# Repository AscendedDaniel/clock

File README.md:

clock
=====

An open source hardware countdown clock.

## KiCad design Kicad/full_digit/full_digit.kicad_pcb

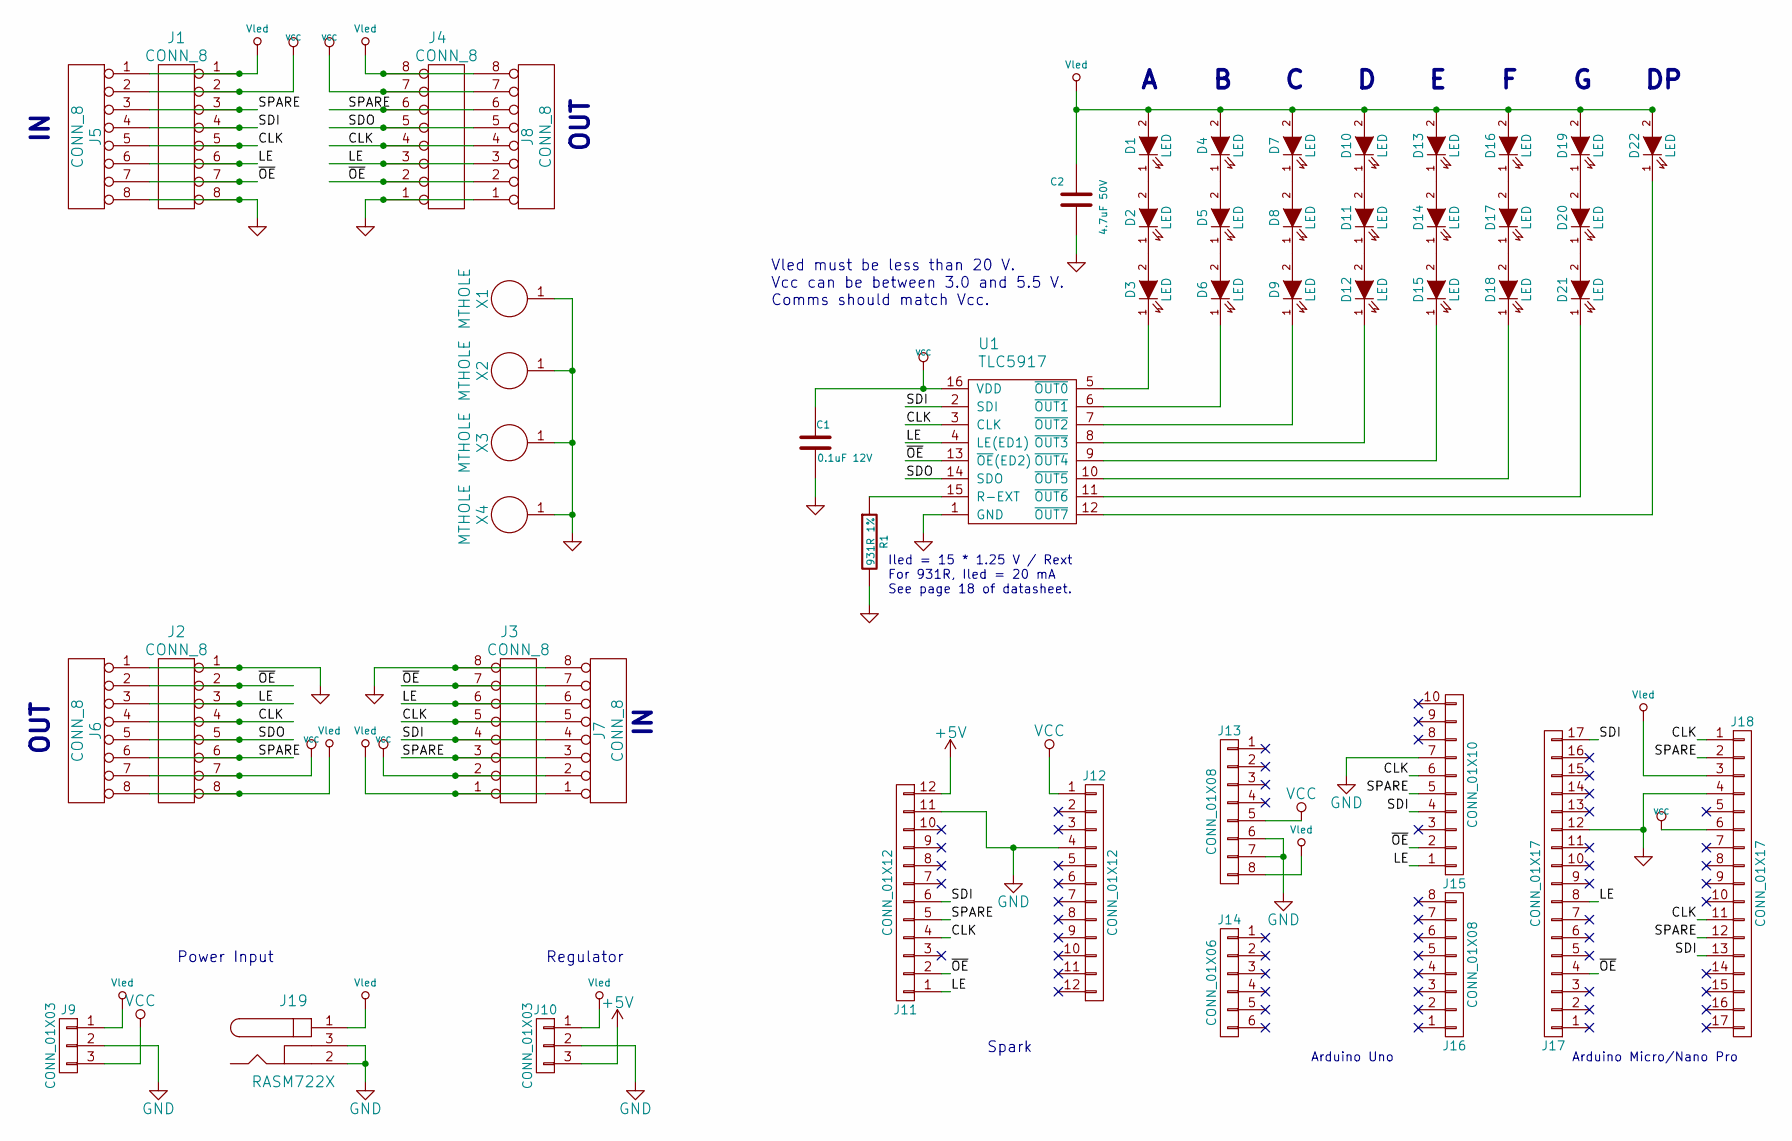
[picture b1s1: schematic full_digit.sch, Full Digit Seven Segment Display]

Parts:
C1: 0.1uF 12V; C_0603
C2: 4.7uF 50V; C_1206_HandSoldering
D1, D2, D3, D4, D5, D6, D7, D8, D9, D10, D11, D12, D13, D14, D15, D16, D17, D18, D19, D20, D21, D22: LED; 1206_LED_Reverse
J1, J2, J3, J4: CONN_8; SSM-SH-08
J5, J6, J7, J8: CONN_8; HEADER_8X1
J9, J10: CONN_01X03; HEADER_SMT_01x03
J11, J12: CONN_01X12; HEADER_SMT_01x12_SV
J13, J16: CONN_01X08; HEADER_SMT_01x08
J14: CONN_01X06; HEADER_SMT_01x06
J15: CONN_01X10; HEADER_SMT_01x10
J17, J18: CONN_01X17; HEADER_SMT_01x17
J19: RASM722X; RASM722
R1: 931R 1%; C_0603
U1: TLC5917; SOIC16_Jason
X1, X2, X3, X4: MTHOLE; MTHOLE_3mm

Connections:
+5V: J10.3, J11.12
/CLK: J1.5, J2.4, J3.5, J4.4, J5.5, J6.4, J7.5, J8.4, J11.4, J15.6, J18.1, J18.11, U1.3 (CLK)
/LE: J1.6, J2.3, J3.6, J4.3, J5.6, J6.3, J7.6, J8.3, J11.1, J15.1, J17.8, U1.4 (LE(ED1))
/SDI: J1.4, J3.4, J5.4, J7.4, J11.6, J15.4, J17.17, J18.13, U1.2 (SDI)
/SDO: J2.5, J4.5, J6.5, J8.5, U1.14 (SDO)
/SPARE: J1.3, J2.6, J3.3, J4.6, J5.3, J6.6, J7.3, J8.6, J11.5, J15.5, J18.2, J18.12
/~OE: J1.7, J2.2, J3.7, J4.2, J5.7, J6.2, J7.7, J8.2, J11.2, J15.2, J17.4, U1.13 (~OE~(ED2))
GND: C1.2, C2.2, J1.8, J2.1, J3.8, J4.1, J5.8, J6.1, J7.8, J8.1, J9.2, J10.2, J11.11, J12.4, J13.6, J13.7, J15.7, J17.12, J18.4, J19.2, J19.3, R1.2, U1.1 (GND), X1.1, X2.1, X3.1, X4.1
unnamed: D1.1 (K), D2.2 (A)
unnamed: D2.1 (K), D3.2 (A)
unnamed: D3.1 (K), U1.5 (~OUT0)
unnamed: D4.1 (K), D5.2 (A)
unnamed: D5.1 (K), D6.2 (A)
unnamed: D6.1 (K), U1.6 (~OUT1)
unnamed: D7.1 (K), D8.2 (A)
unnamed: D8.1 (K), D9.2 (A)
unnamed: D9.1 (K), U1.7 (~OUT2)
unnamed: D10.1 (K), D11.2 (A)
unnamed: D11.1 (K), D12.2 (A)
unnamed: D12.1 (K), U1.8 (~OUT3)
unnamed: D13.1 (K), D14.2 (A)
unnamed: D14.1 (K), D15.2 (A)
unnamed: D15.1 (K), U1.9 (~OUT4)
unnamed: D16.1 (K), D17.2 (A)
unnamed: D17.1 (K), D18.2 (A)
unnamed: D18.1 (K), U1.10 (~OUT5)
unnamed: D19.1 (K), D20.2 (A)
unnamed: D20.1 (K), D21.2 (A)
unnamed: D21.1 (K), U1.11 (~OUT6)
unnamed: D22.1 (K), U1.12 (~OUT7)
unnamed: R1.1, U1.15 (R-EXT)
VCC: C1.1, J1.2, J2.7, J3.2, J4.7, J5.2, J6.7, J7.2, J8.7, J9.3, J12.1, J13.5, J18.6, U1.16 (VDD)
Vled: C2.1, D1.2 (A), D4.2 (A), D7.2 (A), D10.2 (A), D13.2 (A), D16.2 (A), D19.2 (A), D22.2 (A), J1.1, J2.8, J3.1, J4.8, J5.1, J6.8, J7.1, J8.8, J9.1, J10.1, J13.8, J18.3, J19.1

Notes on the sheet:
OUT
Iled = 15 * 1.25 V / Rext For 931R, Iled = 20 mA See page 18 of datasheet.
Vled must be less than 20 V. Vcc can be between 3.0 and 5.5 V. Comms should match Vcc.
Spark
Regulator
Arduino Uno
Arduino Micro/Nano Pro
Power Input

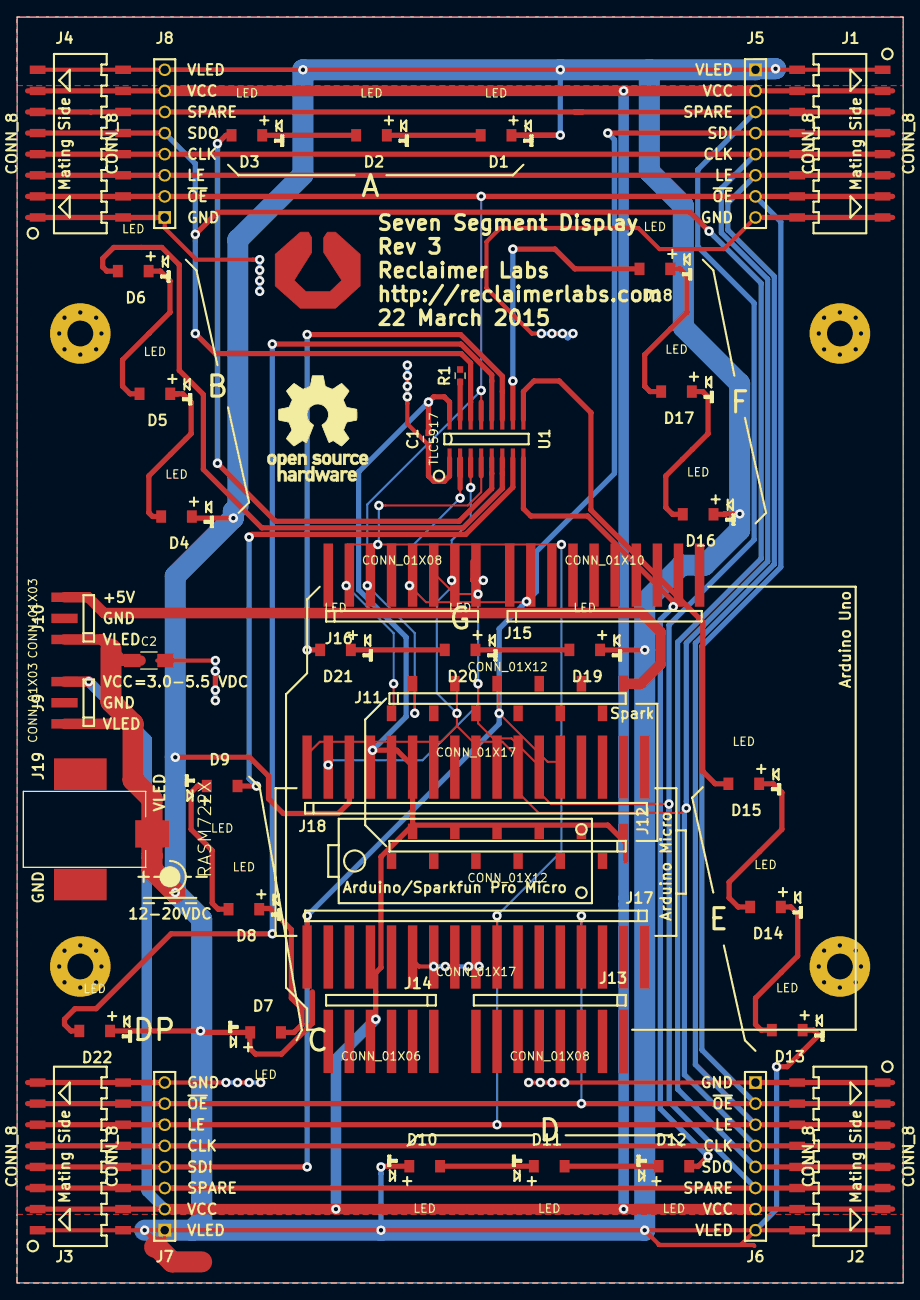
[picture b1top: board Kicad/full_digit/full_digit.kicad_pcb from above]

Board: 2 copper layers, 106.7 x 152.4 mm, 49 parts (0 on the bottom side), 33 nets.

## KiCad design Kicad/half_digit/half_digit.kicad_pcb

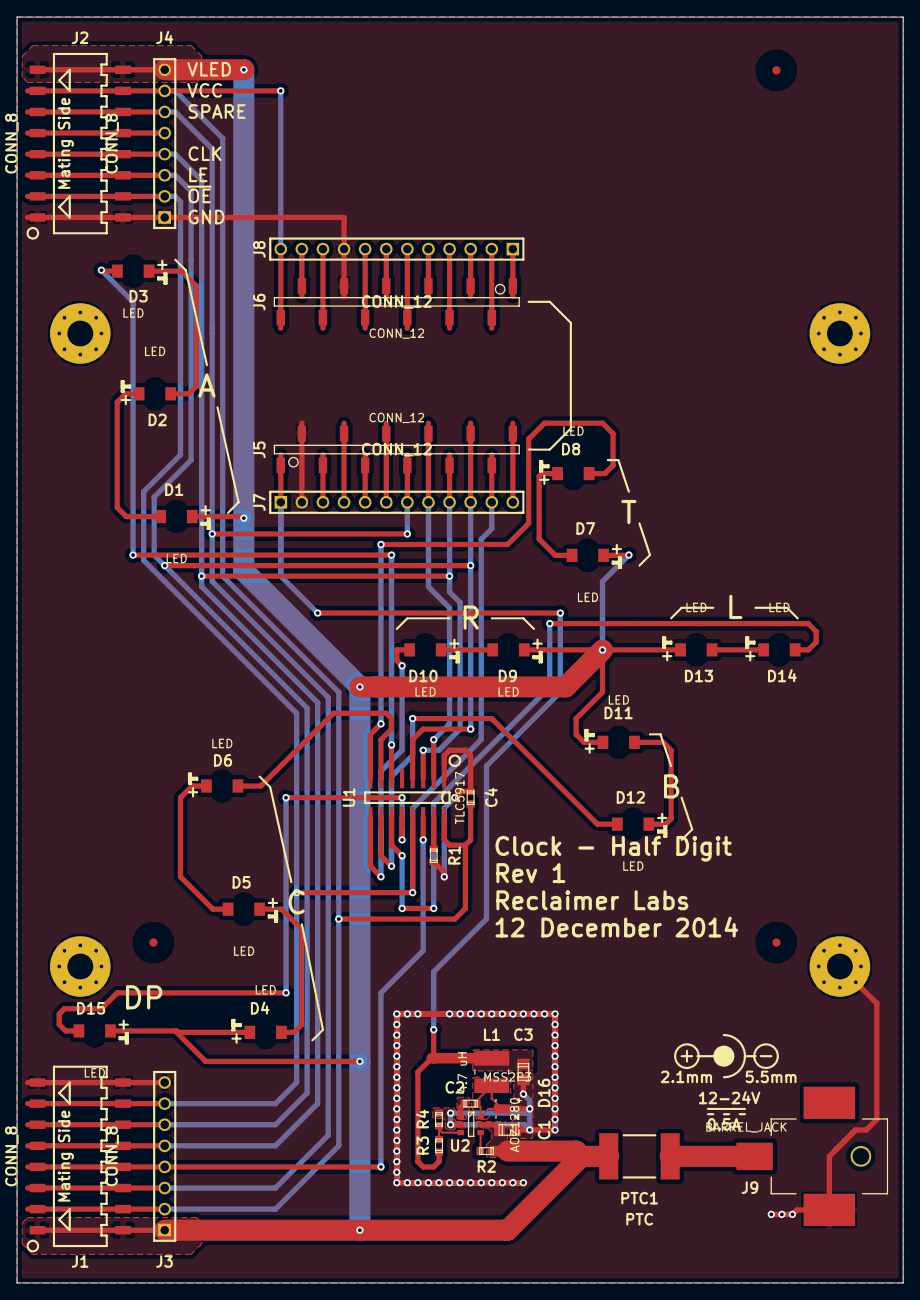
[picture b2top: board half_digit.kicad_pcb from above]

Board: 2 copper layers, 106.7 x 152.4 mm, 44 parts (0 on the bottom side), 47 nets.

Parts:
C1, C3: 4.7uF; c_0805
C2: 10nF; c_0603
C4: 0.1uF; c_0603
D1, D2, D3, D4, D5, D6, D7, D8, D9, D10, D11, D12, D13, D14, D15: LED; 1206_LED_Reverse
D16: MSS2P3
FIDUCIAL: VAL**; FIDUCIAL
FIDUCIAL#2, FIDUCIAL#3: VAL**; FIDUCIAL
J1, J2: CONN_8; SSM-SH-08
J3, J4: CONN_8; HEADER_8X1
J5, J6: CONN_12; SSM-SV-12
J7, J8: CONN_12; HEADER_12X1
J9: BARREL_JACK; PJ-036AH-SMT
L1: 4.7 uH; 1515
PTC1: PTC; 2920_ptc
R1: 931R 1%; c_0603
R2, R4: 9.53k 1%; c_0603
R3: 49.9k 1%; c_0603
U1: TLC5917; SOIC16_Jason
U2: AOZ1280; SOT23_6_Jason
X1, X2, X3, X4: MTHOLE; MTHOLE_3mm

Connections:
+5V: C3.1, J5.1, J7.1, L1.2, R3.1
/CLK: J1.5, J2.4, J3.5, J4.4, J5.9, J7.9, U1.3
/LE: J1.6, J2.3, J3.6, J4.3, J5.10, J7.10, U1.4
/SDI: J5.8, J7.8, U1.2
/SDO: J1.4, J3.4, U1.14
/SPARE: J1.3, J2.6, J3.3, J4.6, J5.7, J7.7
/~OE: J1.7, J2.2, J3.7, J4.2, J5.11, J7.11, U1.13
GND: C1.2, C3.2, C4.2, D16.1, J1.8, J2.1, J3.8, J4.1, J5.2, J6.9, J7.2, J8.9, J9.2, R1.2, R4.2, U1.1, U2.2, X1.1, X2.1, X3.1, X4.1
unnamed: D15.2, U1.12
unnamed: D14.2, U1.11
unnamed: D12.2, U1.10
unnamed: D10.2, U1.9
unnamed: D8.2, U1.8
unnamed: D6.2, U1.7
unnamed: D3.2, U1.6
unnamed: R1.1, U1.15
unnamed: J5.5, J7.5
unnamed: J5.4, J7.4
unnamed: J5.3, J7.3
unnamed: J5.6, J7.6
unnamed: J6.5, J8.5
unnamed: J9.1, PTC1.1
unnamed: J6.11, J8.11
unnamed: J6.10, J8.10
unnamed: J6.8, J8.8
unnamed: J6.7, J8.7
unnamed: J6.6, J8.6
unnamed: J6.4, J8.4
unnamed: J6.3, J8.3
unnamed: J6.2, J8.2
unnamed: J6.1, J8.1
unnamed: J5.12, J7.12
unnamed: R3.2, R4.1, U2.3
unnamed: J2.5, J4.5
unnamed: C2.2, D16.2, L1.1, U2.6
unnamed: C2.1, U2.1
unnamed: R2.2, U2.4
unnamed: D5.2, D6.1
unnamed: D4.2, D5.1
unnamed: D9.2, D10.1
unnamed: D13.2, D14.1
unnamed: D7.2, D8.1
unnamed: D11.2, D12.1
unnamed: D2.2, D3.1
unnamed: D1.2, D2.1
VCC: C4.1, J1.2, J2.7, J3.2, J4.7, J6.12, J8.12, U1.16
Vled: C1.1, D1.1, D4.1, D7.1, D9.1, D11.1, D13.1, D15.1, J1.1, J2.8, J3.1, J4.8, PTC1.2, R2.1, U2.5

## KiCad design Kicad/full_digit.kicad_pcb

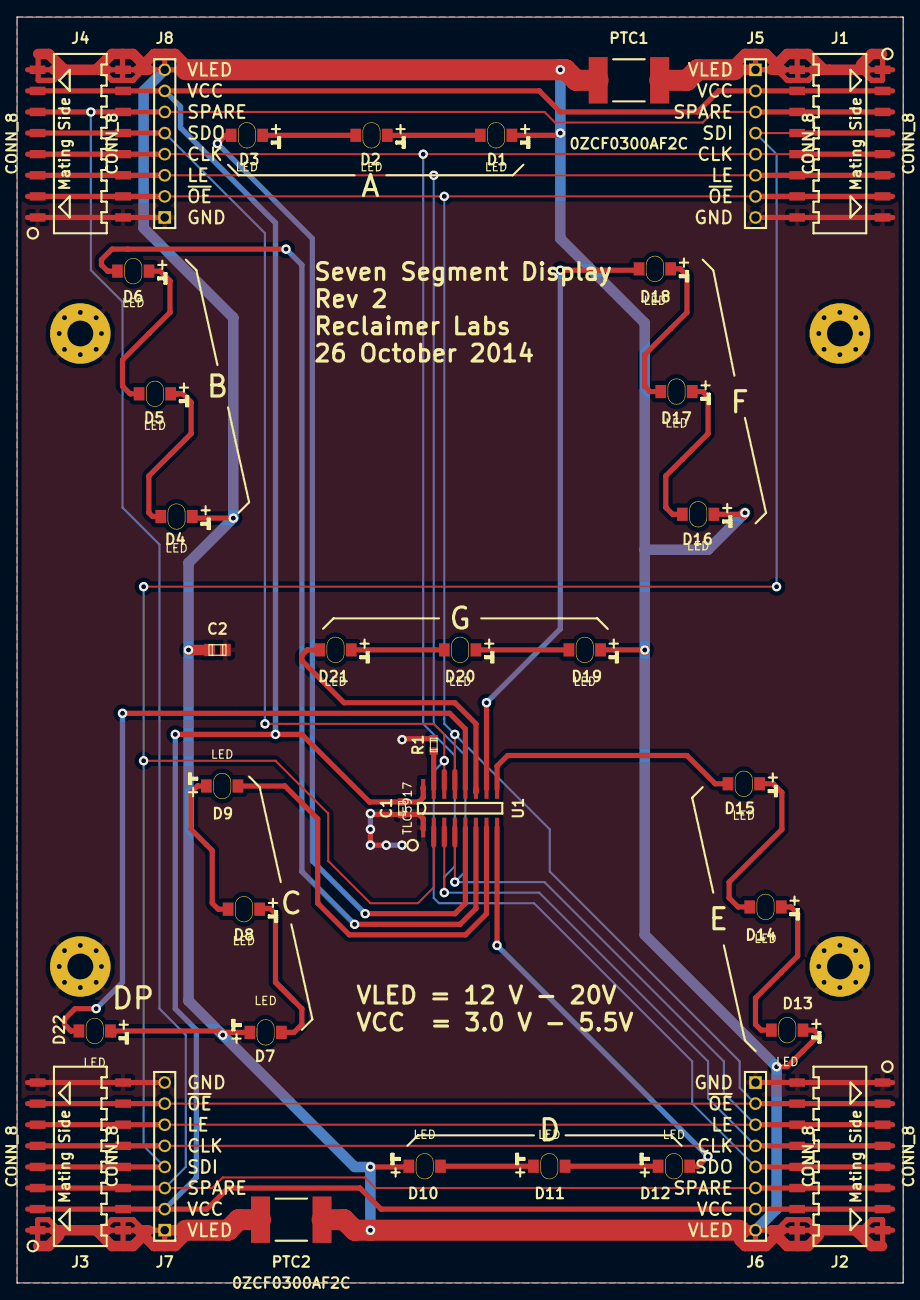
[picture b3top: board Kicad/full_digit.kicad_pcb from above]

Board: 2 copper layers, 106.7 x 152.4 mm, 40 parts (0 on the bottom side), 34 nets.

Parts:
C1: 0.1uF 12V; c_0603
C2: 4.7uF 25V; c_0805
D1, D2, D3, D4, D5, D6, D7, D8, D9, D10, D11, D12, D13, D14, D15, D16, D17, D18, D19, D20, D21, D22: LED; 1206_LED_Reverse
J1, J2, J3, J4: CONN_8; SSM-SH-08
J5, J6, J7, J8: CONN_8; HEADER_8X1
PTC1, PTC2: 0ZCF0300AF2C; 2920_ptc
R1: 931R 1%; c_0603
U1: TLC5917; SOIC16_Jason
X1, X2, X3, X4: MTHOLE; MTHOLE_3mm

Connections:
/CLK: J1.5, J2.4, J3.5, J4.4, J5.5, J6.4, J7.5, J8.4, U1.3
/LE: J1.6, J2.3, J3.6, J4.3, J5.6, J6.3, J7.6, J8.3, U1.4
/SDI: J1.4, J3.4, J5.4, J7.4, U1.2
/SDO: J2.5, J4.5, J6.5, J8.5, U1.14
/SPARE: J1.3, J2.6, J3.3, J4.6, J5.3, J6.6, J7.3, J8.6
/~OE: J1.7, J2.2, J3.7, J4.2, J5.7, J6.2, J7.7, J8.2, U1.13
GND: C1.2, C2.2, J1.8, J2.1, J3.8, J4.1, J5.8, J6.1, J7.8, J8.1, R1.2, U1.1, X1.1, X2.1, X3.1, X4.1
unnamed: R1.1, U1.15
unnamed: D22.2, U1.12
unnamed: D21.2, U1.11
unnamed: D18.2, U1.10
unnamed: D3.2, U1.5
unnamed: D15.2, U1.9
unnamed: D12.2, U1.8
unnamed: D9.2, U1.7
unnamed: D6.2, U1.6
unnamed: D17.2, D18.1
unnamed: D20.2, D21.1
unnamed: D19.2, D20.1
unnamed: D16.2, D17.1
unnamed: D14.2, D15.1
unnamed: D13.2, D14.1
unnamed: J1.1, J5.1, PTC1.1
unnamed: D1.2, D2.1
unnamed: D2.2, D3.1
unnamed: D7.2, D8.1
unnamed: D11.2, D12.1
unnamed: D10.2, D11.1
unnamed: D8.2, D9.1
unnamed: D5.2, D6.1
unnamed: D4.2, D5.1
unnamed: J3.1, J7.1, PTC2.2
VCC: C1.1, J1.2, J2.7, J3.2, J4.7, J5.2, J6.7, J7.2, J8.7, U1.16
Vled: C2.1, D1.1, D4.1, D7.1, D10.1, D13.1, D16.1, D19.1, D22.1, J2.8, J4.8, J6.8, J8.8, PTC1.2, PTC2.1

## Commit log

2014-10-15 Initial Commit
    Initial commit of Kicad files, including project, schematic, board, and
    project-specific library.
2014-10-18 Updated Schematic PDF
2014-10-18 Initial Commit of Test Firmware
    Added two firmware files for Arduino to test seven segment panels.
2014-10-19 Adding BoM
    Initial commit of Bill of Materials for Rev 1 hardware.
2014-10-19 Fix Inter-board Connector
    This fixes the inter-board connector polarity issue (#2) in the
    schematic.
2014-10-19 +5V to Vcc
    Fix for Issue +13 in schematic.
2014-10-19 Added fuses
    Added two PTC resettable fuses, one to each input terminal. This
    resolves issue #3. The extra resistance is a maximum of 50 mOhm per PTC
    under normal conditions. This reduces the maximum number of series
    panels from 25 to 17 between additional power connectors are needed. The
    trip current is 3 A.
2014-10-21 Updated Decoupling Capacitors
    Updated the decoupling capacitors and consolidated C2-C5 into C2. One
    4.7uF cap should be enough to ensure that the voltage drop resulting
    from all segments off to all segments on remains less than 1 V while the
    power supply compensates. C1 decouples U1, which has a maximum clock
    frequency of 30 MHz, but will be operating well under that for most
    applications. One standard 0.1uF cap on the Vcc rail should be enough.
2014-10-21 Updated Footprints for Rev 2
2014-10-21 Rev 2 Layout Start
    U1 is rotated as per issue #6. Mounting holes have been moved as per
    issue #8.
2014-10-24 Mechanical and Logo Updates
    Updated Reclaimer Labs Logo as per issue #11. Also added thru-hole
    connectors to layout as per issue #9. Mounting holes have been moved as
    per issue #8. LED hole is replaced with slot as per issue #7, might need
    to be tweaked to reduce rotation during assembly. Inter-board connector
    silkscreen is updated to more easily show mating side vs non-mating side
    as per issue #5. Initial commit of gerbers.
2014-10-26 Added pin labels
    Added labels on all input and output pins as per issue #5.
2014-10-26 Removed test points
    Removed test points T0-T7. They are unnecessary, as the pins on U1 and
    the LEDs provide a good enough interface. If they are needed for
    pogo-pin type testing, they can be added back in.
2014-10-26 Rev 2 Feature Complete
    Possible final draft of Rev 2 layout.
2014-10-27 Layout Tweaks
    Updated silkscreen to include voltage ranges. Updated tracks into all
    parts to balance and center tracks in and out.
2014-10-27 Gerber packing
    Packing two version of the gerbers. One for more full-service
    manufactures with assembly drawings, notes, and maps. The other is the
    RS274X gerbers for more automated manufacturers.
2014-11-02 Initial Commit of Half Digit
    Organized the folders and added the schematic for the half digit.
2014-11-03 Partial Layout
    LEDs, inter-board connectors, and buck converter placed. Still need to
    figure out placement of DC jack.
2014-11-05 Rough draft of half digit layout
2014-11-25 Initial Check-in of Enclosure
2014-12-13 Half Digit Work
    Moved spark landing pads to not interfere with L-bracket from OpenBeam
    frame.
2015-02-26 Firmware and Documentation Updates
2015-03-03 Added new connectors to schematics
    Added DNS connectors for Spark Core/Photon/Electron, Arduino
    Uno/Micro/Nano. Also redacted access token for the Spark Core used for
    the prototype clock. That Spark has been destroyed, so don't bother
    trying to use the token.
2015-03-14 Placement of Rev 3
    Placed new parts: Spark, Arduino Uno, Arduino Micro, and logo. Routing
    still to do.
2015-03-25 Rev 3 Final Draft
2015-05-04 Firmware Updates
    Updated firmware to be consistent with the Rev 3 built-in pads for
    Arduino and Spark.
2015-05-08 First Rev 4 fixes
    * Added NPTH for barrel connector as per issue #21
    * Connected shunt and sleeve together to increase chances of capability
    with barrel connectors as per issue #20
    * Lengthen Arduino pads and double-checked spacing as per issue #19
    * Fixed spacing for Spark Cores as per issue #18
    * Updated C2 to 1206 as per issue #17
2015-05-08 Updated controller pads
